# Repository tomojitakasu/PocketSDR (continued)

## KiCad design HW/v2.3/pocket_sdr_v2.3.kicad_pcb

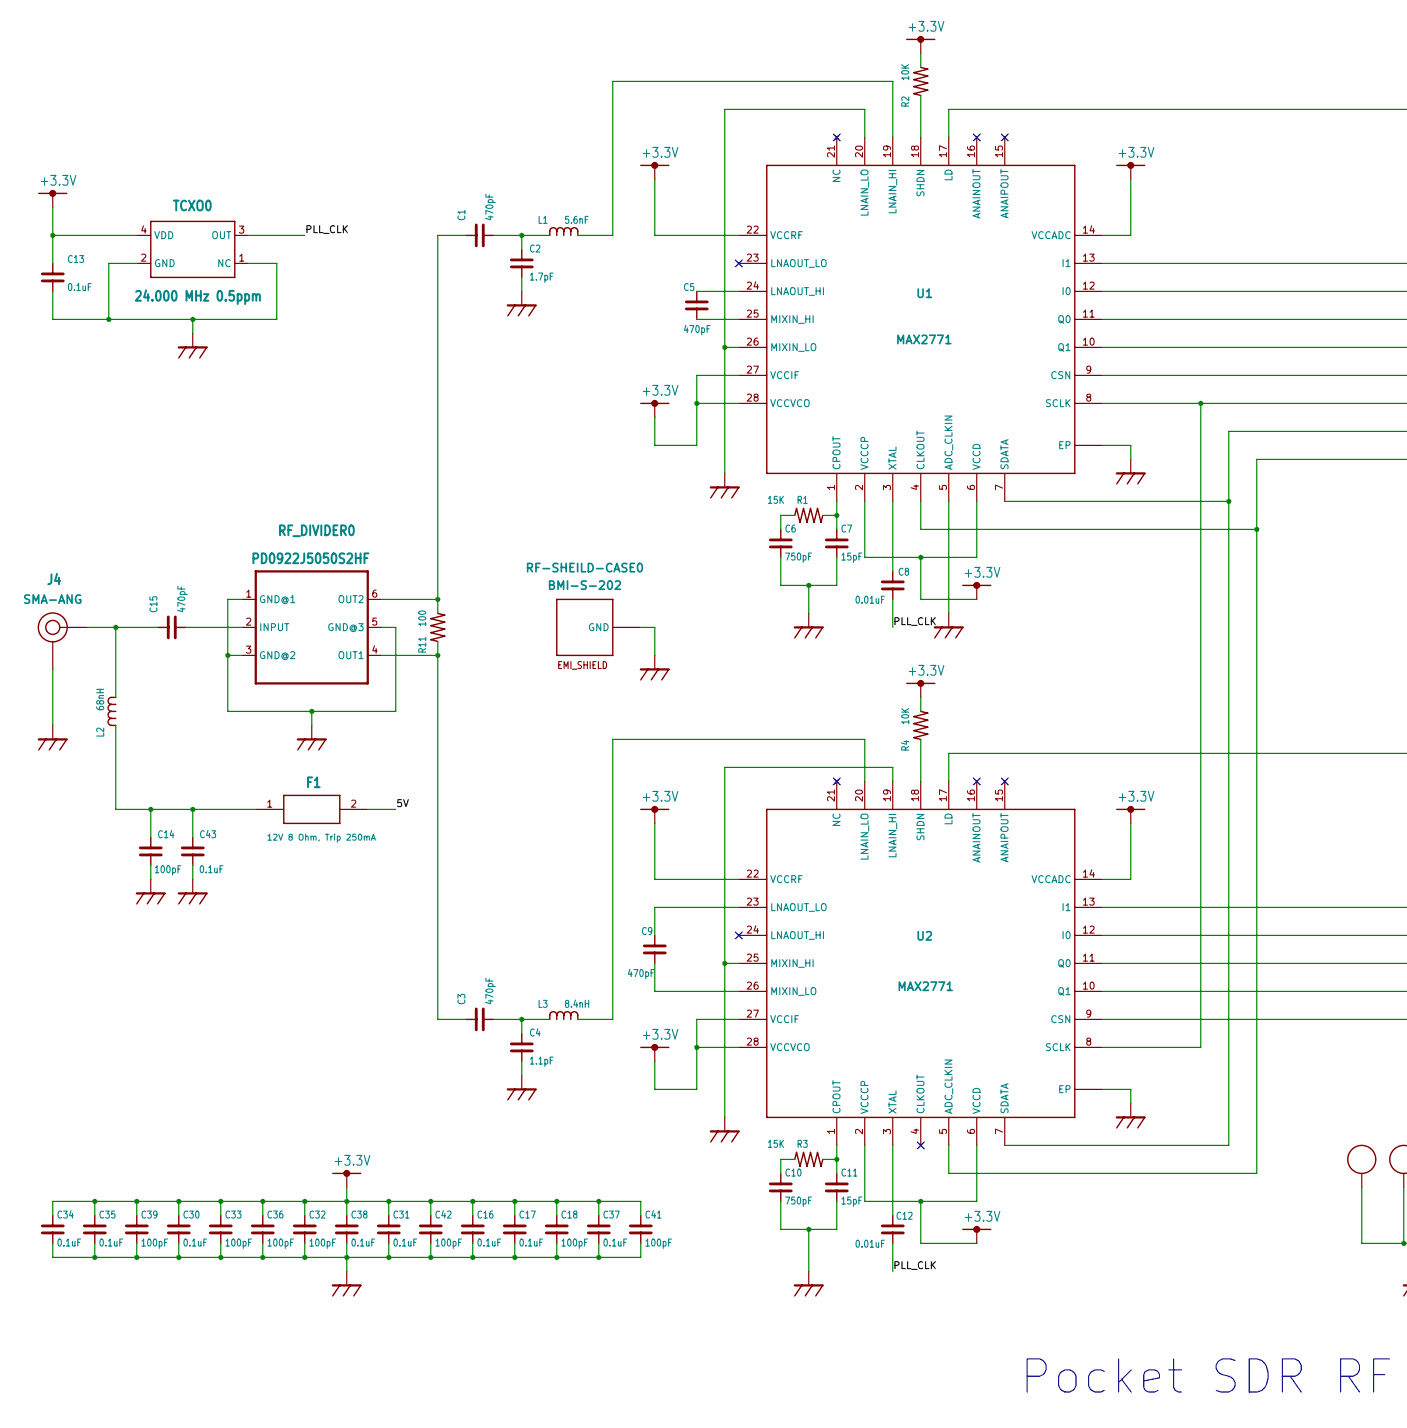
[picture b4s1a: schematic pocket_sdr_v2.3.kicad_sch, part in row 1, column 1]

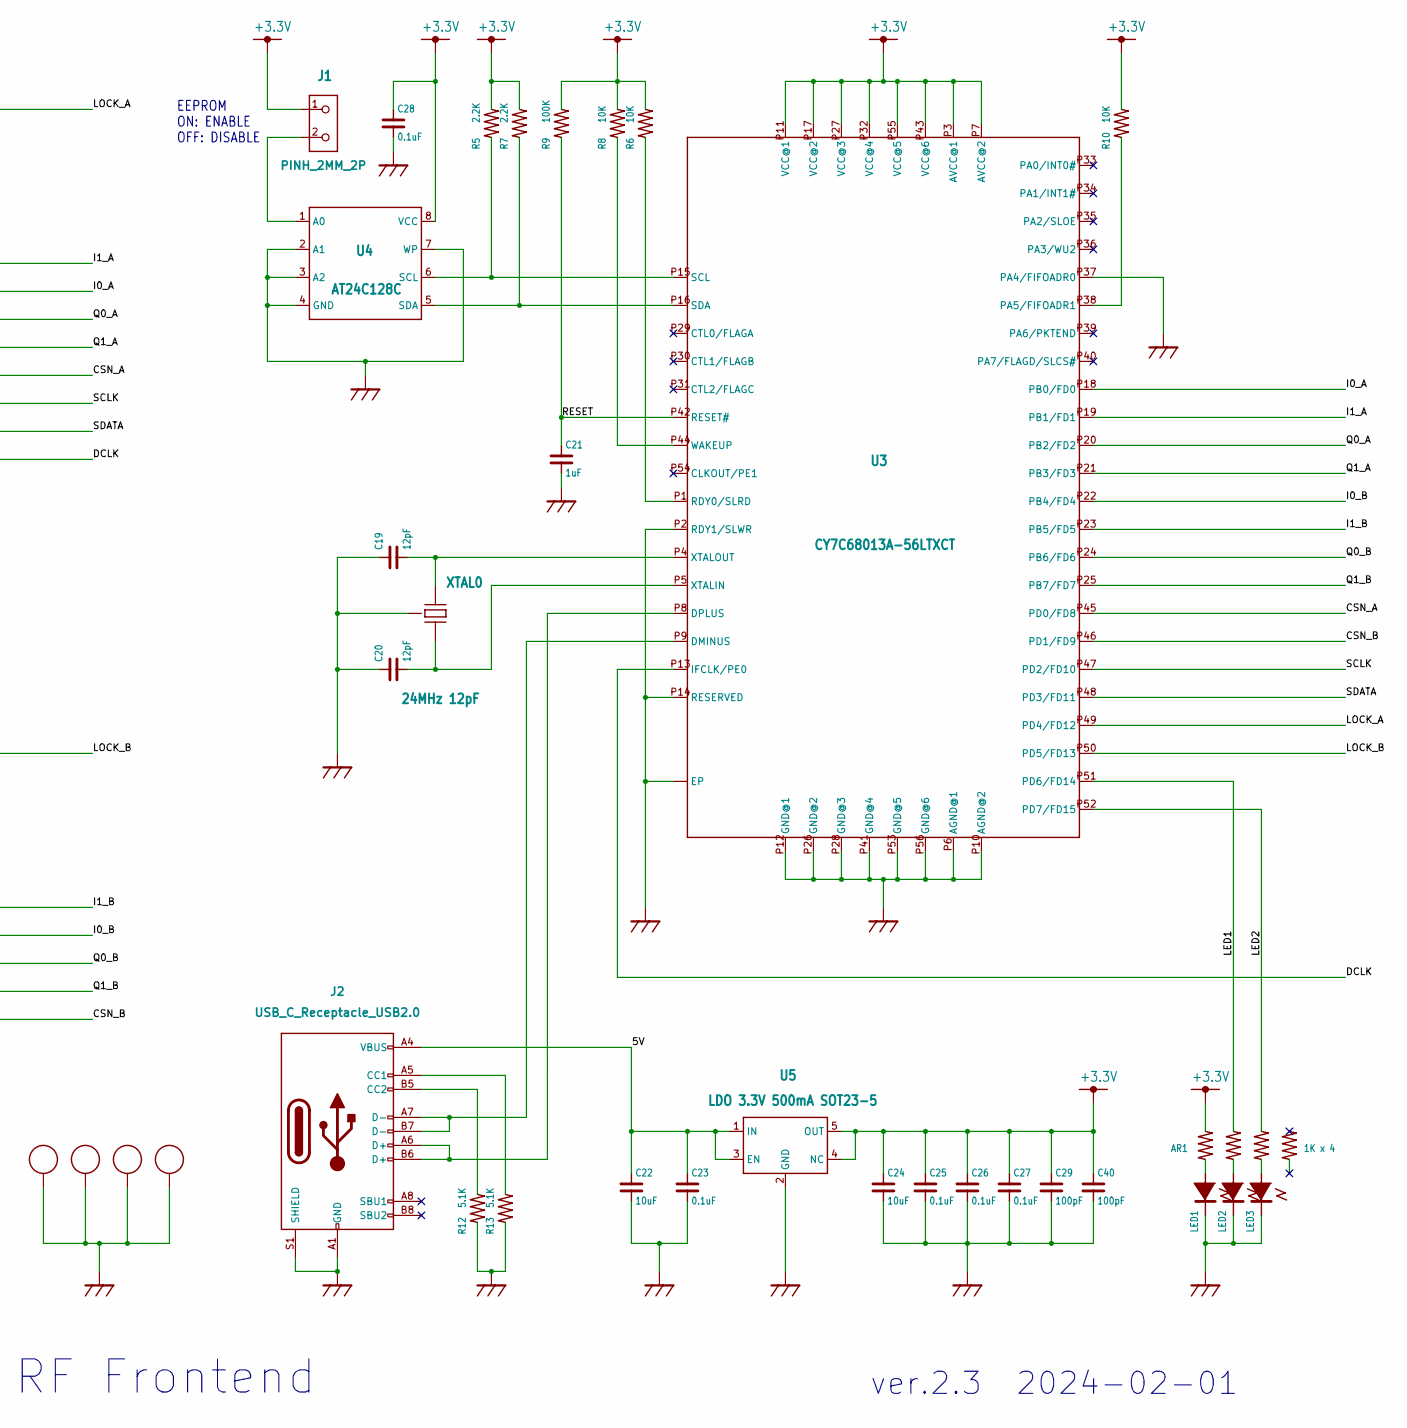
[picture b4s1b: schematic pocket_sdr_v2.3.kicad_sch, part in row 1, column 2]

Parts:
AR1: 1K x 4; EXB28V
C1, C3, C5, C9, C15: 470pF; C1005
C2: 1.7pF; C1005
C4: 1.1pF; C1005
C6, C10: 750pF; C1005
C7, C11: 15pF; C1005
C8, C12: 0.01uF; C1005
C13, C16, C17, C23, C25, C26, C27, C28, C30, C31, C34, C35, C37, C38, C43: 0.1uF; C1005
C14, C18, C29, C32, C33, C36, C39, C40, C41, C42: 100pF; C1005
C19, C20: 12pF; C1005
C21: 1uF; C1005
C22, C24: 10uF; C3225
F1: 12V 8 Ohm, Trip 250mA; C1608
J1: PINH_2MM_2P; PINH-2MM-2P
J2: USB_C_Receptacle_USB2.0
J4: SMA-ANG
L1: 5.6nF; C1608
L2: 68nH; C1608
L3: 8.4nH; C1608
LED1, LED2, LED3: LED1608; LED_1608
R1, R3: 15K; C1005
R2, R4, R6, R8, R10: 10K; C1005
R5, R7: 2.2K; C1005
R9: 100K; C1005
R11: 100; C1005
R12, R13: 5.1K; C1005
RF-SHEILD-CASE0: BMI-S-202
RF_DIVIDER0: PD0922J5050S2HF; RF_DIV
TCXO0: 24.000 MHz 0.5ppm; TCXO
U1, U2: MAX2771; TQFN28
U3: CY7C68013A-56LTXCT; QFN56
U4: AT24C128C; TSSOP_8P
U5: LDO 3.3V 500mA SOT23-5; SOT23
XTAL0: 24MHz 12pF; XTAL_SMD

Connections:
+3.3V: AR1.2, C13.1, C16.1, C17.1, C18.1, C24.P$1 (1), C25.1, C26.1, C27.1, C28.1, C29.1, C30.1, C31.1, C32.1, C33.1, C34.1, C35.1, C36.1, C37.1, C38.1, C39.1, C40.1, C41.1, C42.1, J1.1, R2.2, R4.2, R5.2, R6.2, R7.2, R8.2, R9.2, R10.2, TCXO0.4 (VDD), U1.2 (VCCCP), U1.6 (VCCD), U1.14 (VCCADC), U1.22 (VCCRF), U1.27 (VCCIF), U1.28 (VCCVCO), U2.2 (VCCCP), U2.6 (VCCD), U2.14 (VCCADC), U2.22 (VCCRF), U2.27 (VCCIF), U2.28 (VCCVCO), U3.P3 (AVCC@1), U3.P7 (AVCC@2), U3.P11 (VCC@1), U3.P17 (VCC@2), U3.P27 (VCC@3), U3.P32 (VCC@4), U3.P43 (VCC@6), U3.P55 (VCC@5), U4.8 (VCC), U5.4 (NC), U5.5 (OUT)
/5V: C22.P$1 (1), C23.1, F1.2, J2.A4 (VBUS), J2.A9 (VBUS), J2.B4 (VBUS), J2.B9 (VBUS), U5.1 (IN), U5.3 (EN)
/CSN_A: U1.9 (CSN), U3.P45 (PD0/FD8)
/CSN_B: U2.9 (CSN), U3.P46 (PD1/FD9)
/DCLK: U1.4 (CLKOUT), U2.5 (ADC_CLKIN), U3.P13 (IFCLK/PE0)
/I0_A: U1.12 (I0), U3.P18 (PB0/FD0)
/I0_B: U2.12 (I0), U3.P22 (PB4/FD4)
/I1_A: U1.13 (I1), U3.P19 (PB1/FD1)
/I1_B: U2.13 (I1), U3.P23 (PB5/FD5)
/LED1: AR1.4, U3.P51 (PD6/FD14)
/LED2: AR1.6, U3.P52 (PD7/FD15)
/LOCK_A: U1.17 (LD), U3.P49 (PD4/FD12)
/LOCK_B: U2.17 (LD), U3.P50 (PD5/FD13)
/PLL_CLK: C8.1, C12.1, TCXO0.3 (OUT)
/Q0_A: U1.11 (Q0), U3.P20 (PB2/FD2)
/Q0_B: U2.11 (Q0), U3.P24 (PB6/FD6)
/Q1_A: U1.10 (Q1), U3.P21 (PB3/FD3)
/Q1_B: U2.10 (Q1), U3.P25 (PB7/FD7)
/RESET: C21.1, R9.1, U3.P42 (RESET#)
/SCLK: U1.8 (SCLK), U2.8 (SCLK), U3.P47 (PD2/FD10)
/SDATA: U1.7 (SDATA), U2.7 (SDATA), U3.P48 (PD3/FD11)
GND: C2.1, C4.2, C6.2, C7.2, C10.2, C11.2, C13.2, C14.1, C16.2, C17.2, C18.2, C19.1, C20.1, C21.2, C22.P$2 (2), C23.2, C24.P$2 (2), C25.2, C26.2, C27.2, C28.2, C29.2, C30.2, C31.2, C32.2, C33.2, C34.2, C35.2, C36.2, C37.2, C38.2, C39.2, C40.2, C41.2, C42.2, C43.1, J2.A1 (GND), J2.A12 (GND), J2.B1 (GND), J2.B12 (GND), J2.S1 (SHIELD), J4.P2 (GND), J4.P3 (GND), J4.P4 (GND), J4.P5 (GND), LED1.2, LED2.2, LED3.2, R12.1, R13.1, RF-SHEILD-CASE0.P1 (GND), RF-SHEILD-CASE0.P2 (GND), RF-SHEILD-CASE0.P3 (GND), RF-SHEILD-CASE0.P4 (GND), RF-SHEILD-CASE0.P5 (GND), RF-SHEILD-CASE0.P6 (GND), RF-SHEILD-CASE0.P7 (GND), RF-SHEILD-CASE0.P8 (GND), RF-SHEILD-CASE0.P9 (GND), RF-SHEILD-CASE0.P10 (GND), RF-SHEILD-CASE0.P11 (GND), RF-SHEILD-CASE0.P12 (GND), RF_DIVIDER0.1 (GND@1), RF_DIVIDER0.3 (GND@2), RF_DIVIDER0.5 (GND@3), TCXO0.1 (NC), TCXO0.2 (GND), U1.5 (ADC_CLKIN), U1.20 (LNAIN_LO), U1.26 (MIXIN_LO), U1.C1 (EP), U1.C2 (EP), U1.C3 (EP), U1.C4 (EP), U1.EP, U1.V1 (EP), U1.V2 (EP), U1.V3 (EP), U1.V4 (EP), U1.V5 (EP), U1.V6 (EP), U1.V7 (EP), U1.V8 (EP), U1.V9 (EP), U2.19 (LNAIN_HI), U2.25 (MIXIN_HI), U2.C1 (EP), U2.C2 (EP), U2.C3 (EP), U2.C4 (EP), U2.EP, U2.V1 (EP), U2.V2 (EP), U2.V3 (EP), U2.V4 (EP), U2.V5 (EP), U2.V6 (EP), U2.V7 (EP), U2.V8 (EP), U2.V9 (EP), U3.EP1 (EP), U3.EP2 (EP), U3.EP3 (EP), U3.EP4 (EP), U3.EP5 (EP), U3.P2 (RDY1/SLWR), U3.P6 (AGND@1), U3.P10 (AGND@2), U3.P12 (GND@1), U3.P14 (RESERVED), U3.P26 (GND@2), U3.P28 (GND@3), U3.P37 (PA4/FIFOADR0), U3.P41 (GND@4), U3.P53 (GND@5), U3.P56 (GND@6), U3.P$1 (EP), U3.P$2 (EP), U3.P$3 (EP), U3.P$4 (EP), U3.P$5 (EP), U3.P$6 (EP), U3.P$7 (EP), U3.P$8 (EP), U3.P$9 (EP), U3.P$10 (EP), U3.P$11 (EP), U3.P$12 (EP), U3.P$13 (EP), U3.P$14 (EP), U3.P$15 (EP), U3.P$16 (EP), U3.P$17 (EP), U3.P$18 (EP), U3.P$19 (EP), U3.P$20 (EP), U4.2 (A1), U4.3 (A2), U4.4 (GND), U4.7 (WP), U5.2 (GND), XTAL0.P2 (GND), XTAL0.P4 (GND)
unnamed: AR1.1, LED1.1 (+)
unnamed: AR1.3, LED2.1 (+)
unnamed: AR1.5, LED3.1 (+)
unnamed: C14.2, C43.2, F1.1, L2.1
unnamed: J1.2, U4.1 (A0)
unnamed: J2.A5 (CC1), R13.2
unnamed: J2.B5 (CC2), R12.2
unnamed: C15.1, J4.P1 (RF), L2.2
unnamed: C1.2, C2.2, L1.1
unnamed: L1.2, U1.19 (LNAIN_HI)
unnamed: C3.2, C4.1, L3.1
unnamed: L3.2, U2.20 (LNAIN_LO)
unnamed: C6.1, R1.1
unnamed: C7.1, R1.2, U1.1 (CPOUT)
unnamed: R2.1, U1.18 (SHDN)
unnamed: C10.1, R3.1
unnamed: C11.1, R3.2, U2.1 (CPOUT)
unnamed: R4.1, U2.18 (SHDN)
unnamed: R5.1, U3.P15 (SCL), U4.6 (SCL)
unnamed: R6.1, U3.P1 (RDY0/SLRD)
unnamed: R7.1, U3.P16 (SDA), U4.5 (SDA)
unnamed: R8.1, U3.P44 (WAKEUP)
unnamed: R10.1, U3.P38 (PA5/FIFOADR1)
unnamed: C3.1, R11.1, RF_DIVIDER0.4 (OUT1)
unnamed: C1.1, R11.2, RF_DIVIDER0.6 (OUT2)
unnamed: C15.2, RF_DIVIDER0.2 (INPUT)
unnamed: C5.1, U1.24 (LNAOUT_HI)
unnamed: C5.2, U1.25 (MIXIN_HI)
unnamed: C8.2, U1.3 (XTAL)
unnamed: C9.1, U2.23 (LNAOUT_LO)
unnamed: C9.2, U2.26 (MIXIN_LO)
unnamed: C12.2, U2.3 (XTAL)
unnamed: J2.A7 (D-), J2.B7 (D-), U3.P9 (DMINUS)
unnamed: J2.A6 (D+), J2.B6 (D+), U3.P8 (DPLUS)
unnamed: C20.2, U3.P5 (XTALIN), XTAL0.P3 (XTAL2)
unnamed: C19.2, U3.P4 (XTALOUT), XTAL0.P1 (XTAL1)

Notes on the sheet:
Pocket SDR RF Frontend
EEPROM ON: ENABLE OFF: DISABLE
ver.2.3 2024-02-01

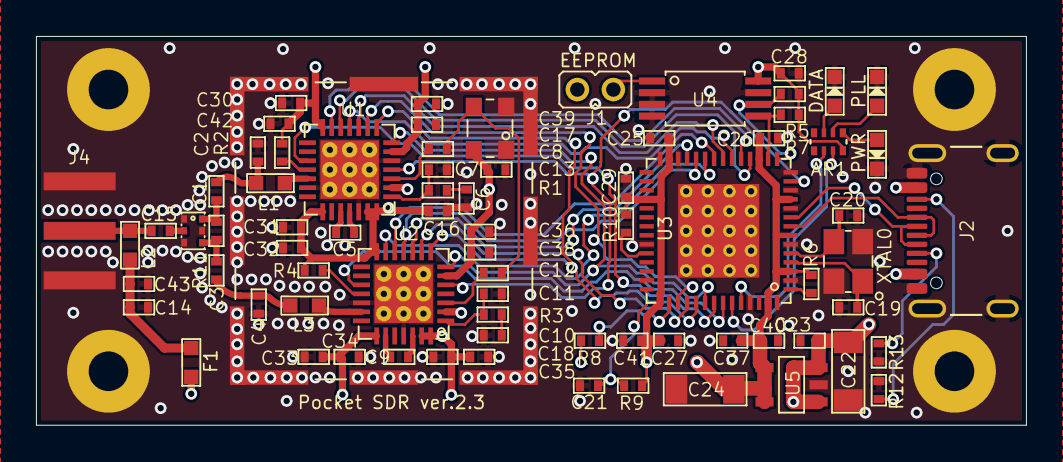
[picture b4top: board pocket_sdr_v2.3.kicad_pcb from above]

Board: 4 copper layers, 55.0 x 21.6 mm, 76 parts (0 on the bottom side), 58 nets.

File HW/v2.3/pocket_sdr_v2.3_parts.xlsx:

No | Part | Value | Package | Qty | Assembly | Supplier | Supplier Part # | Digi-Key Part # | Unit Price(Yen) | Price(Yen) | URL | NOTE
1 | U1, U2 | MAX2771 | TQFN28 | 2 | 2 | Maxim | MAX2771ETI+ | MAX2771ETI+-ND | 1631 | 3262 | https://www.digikey.jp/products/ja?keywords=MAX2771ETI%2B-ND
2 | U3 | EZ-USB FX2LP QFN56 | QFN56 | 1 | 1 | Cypress | CY7C68013A-56LTXCT | 428-4634-1-ND | 1857 | 1857 | https://www.digikey.jp/product-detail/ja/cypress-semiconduct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
3 | U4 | EEPROM 128Kbit I2C 8TSSOP | TSSOP_8P | 1 | 1 | Microchip | AT24C128C-XHM-T | AT24C128C-XHM-TCT-ND | 84 | 84 | https://www.digikey.jp/product-detail/ja/microchip-technolog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
4 | U5 | LDO 3.3V 500mA SOT23-5 | SOT23-5 | 1 | 1 | Nisshinbo | RP111N331D-TR-FE | 2129-RP111N331D-TR-FECT-ND | 171 | 171 | https://www.digikey.jp/products/ja?keywords=2129-RP111N331D-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
5 | RF_DIVIDER0 | 0805 Power Divider 50ohm 950 - 2150 MHz | 2.04 x 1.29 SMD | 1 | 1 | Anaren | PD0922J5050S2HF | 1173-1094-1-ND | 160 | 160 | https://www.digikey.jp/product-detail/ja/anaren/PD0922J5050S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
6 | TCXO0 | TCXO 24.000 MHz | 3.2 x 2.5 SMD | 1 | 1 | Epson | TG2520SMN 24.0000M-MCGNNM3 | - | 526.29999999999995 | 526.29999999999995 | https://www.mouser.jp/ProductDetail/Epson-Timing/TG2520SMN-2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
7 | XTAL0 | XTAL 24MHz SMD 12pF | 3.4 x 2.7 SMD | 1 | 1 | Wurth | 830108340709 | 1923-830108340709CT-ND | 126 | 126 | https://www.digikey.jp/products/ja?keywords=1923-830108340709CT-ND
8 | R1, R3 | 15K | R1005 | 2 | 2 | YAGEO | RC0402JR-0715KL | 311-15KJRCT-ND | 2.8 | 5.6 | https://www.digikey.jp/ja/products/detail/yageo/RC0402JR-071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
9 | R2, R4, R6, R8, R10 | 10K | R1005 | 5 | 5 | YAGEO | RC0402JR-0710KL | 311-10KJRCT-ND | 2.8 | 14 | https://www.digikey.jp/ja/products/detail/yageo/RC0402JR-071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
10 | R5, R7 | 2.2K | R1005 | 2 | 2 | YAGEO | RC0402JR-072K2L | 311-2.2KJRCT-ND | 2.8 | 5.6 | https://www.digikey.jp/ja/products/detail/yageo/RC0402JR-072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
11 | R9 | 100K | R1005 | 1 | 1 | YAGEO | RC0402JR-07100KL | 311-100KJRCT-ND | 2.8 | 2.8 | https://www.digikey.jp/ja/products/detail/yageo/RC0402JR-071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
12 | R11 | 100 | R1005 | 1 | 1 | YAGEO | RC0402JR-07100RL | 311-100JRCT-ND | 2.9 | 2.9 | https://www.digikey.jp/ja/products/detail/yageo/RC0402JR-071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
13 | R12, R13 | 5.1K | R1005 | 2 | 2 | YAGEO | RC0402FR-135K1L | 13-RC0402FR-135K1LCT-ND | 2.2999999999999998 | 4.5999999999999996 | https://www.digikey.jp/ja/products/detail/yageo/RC0402FR-135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
14 | AR1 | 1K x 4 RES ARRAY | EXB28V | 1 | 1 | Panasonic | EXB-28V102JX | Y7102CT-ND | 16 | 16 | https://www.digikey.jp/products/ja?keywords=Y7102CT-ND
15 | C1, C3, C5, C9, C15 | 470pF | C1005 | 5 | 5 | Kyocera | KGM05AR71H471KH | 478-KGM05AR71H471KHCT-ND | 4.5 | 22.5 | https://www.digikey.jp/ja/products/detail/kyocera-avx/KGM05A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
16 | C2 | 1.7pF | C1005 | 1 | 1 | Murata | GJM1555C1H1R7BB01D | 490-6074-1-ND | 10.6 | 10.6 | https://www.digikey.jp/ja/products/detail/murata-electronics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
17 | C4 | 1.1pF | C1005 | 1 | 1 | YAGEO | CC0402BRNPO9BN1R1 | 311-3321-1-ND | 6.2 | 6.2 | https://www.digikey.jp/ja/products/detail/yageo/CC0402BRNPO9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
18 | C6, C10 | 750pF | C1005 | 2 | 2 | Taiyo Yuden | UMK105CH751JVHF | 587-5098-1-ND | 11.1 | 22.2 | https://www.digikey.jp/ja/products/detail/taiyo-yuden/UMK105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
19 | C7, C11 | 15pF | C1005 | 2 | 2 | Kyocera | KGM05ACG1H150JH | 478-KGM05ACG1H150JHCT-ND | 5.0999999999999996 | 10.199999999999999 | https://www.digikey.jp/ja/products/detail/kyocera-avx/KGM05A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
20 | C8, C12 | 0.01uF | C1005 | 2 | 2 | Kyocera | KGM05AR71C103KH | 478-KGM05AR71C103KHCT-ND | 2 | 4 | https://www.digikey.jp/ja/products/detail/kyocera-avx/KGM05A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
21 | C13, C16, C17, C23, C25, C26, C27, C28, C30, C31, C34, C35, C37, C38, C43 | 0.1uF | C1005 | 15 | 15 | Kyocera | KGM05AR71C104KH | 478-KGM05AR71C104KHCT-ND | 2.2000000000000002 | 33 | https://www.digikey.jp/ja/products/detail/kyocera-avx/KGM05A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
22 | C14, C18, C29, C32, C33, C36, C39, C40, C41, C42 | 100pF | C1005 | 10 | 10 | Kyocera | KGM05ACG1H101JH | 478-KGM05ACG1H101JHCT-ND | 3.7 | 37 | https://www.digikey.jp/ja/products/detail/kyocera-avx/KGM05A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
23 | C19, C20 | 12pF | C1005 | 2 | 2 | Kyocera | KGM05ACG1H120JH | 478-KGM05ACG1H120JHCT-ND | 1.6 | 3.2 | https://www.digikey.jp/ja/products/detail/kyocera-avx/KGM05A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
24 | C21 | 1uF | C1005 | 1 | 1 | Kyocera | KGM05AR51A105KH | 478-KGM05AR51A105KHCT-ND | 11 | 11 | https://www.digikey.jp/ja/products/detail/kyocera-avx/KGM05A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
25 | C22, C24 | 10uF | C3216 | 2 | 2 | Samsung | CL31B106MOHNNNE | 1276-6641-1-ND | 20.399999999999999 | 40.799999999999997 | https://www.digikey.jp/ja/products/detail/samsung-electro-me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
26 | L1 | 5.6nH | L1608 | 1 | 1 | Murata | LQW18AN5N6D00D | 490-1164-1-ND | 23 | 23 | https://www.digikey.jp/ja/products/detail/murata-electronics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
27 | L2 | 68nH | L1608 | 1 | 1 | Murata | LQW18AN68NJ00D | 490-1178-1-ND | 23 | 23 | https://www.digikey.jp/ja/products/detail/murata-electronics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
28 | L3 | 8.4nH | L1608 | 1 | 1 | Murata | LQW18AN8N4C8ZD | 490-15752-1-ND | 39 | 39 | https://www.digikey.jp/ja/products/detail/murata-electronics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
29 | LED1, LED2, LED3 | LED1608 White | LED1608 | 3 | 3 | QT Brightek | QBLP601-IW | 1516-1057-1-ND | 59 | 177 | https://www.digikey.jp/ja/products/detail/qt-brightek-qtb/QB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
30 | J1 | PIN HEADER 2MM 2P | PINH-2MM-2P | 1 | 0 | Harwin | M22-2510205 | 952-1311-ND | 31 | 31 | https://www.digikey.jp/ja/products/detail/harwin-inc/M22-251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
31 | J2 | USB-C RECEPTACLE SMT USB2.0 | USB-C SMT | 1 | 1 | GCT | USB4105-GF-A | 2073-USB4105-GF-ACT-ND | 126 | 126 | https://www.digikey.jp/ja/products/detail/gct/USB4105-GF-A/11198441
32 | J4 | SMA JACK EDGE MNT | SMA JACK EDGE MNT | 1 | 0 | uxcell | - | - | 157.6 | 157.6 | https://www.amazon.co.jp/uxcell-a11053100ux0317-RF%E3%82%B3%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
33 | J1-S | CONN SHUNT 2MM | CONN SHUNT 2MM | 1 | 0 | Sullins Connector | SPN02SYBN-RC | S3404-ND | 20 | 20 | https://www.digikey.jp/ja/products/detail/sullins-connector-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
34 | RF-SHEILD-CASE | RF SHIELD 0.65" x 0.65" SOLDER | 0.65" x 0.65" | 1 | 0 | Laird | BMI-S-202-F | 903-1051-1-ND | 312 | 312 | https://www.digikey.jp/products/ja?keywords=903-1051-1-ND
35 | RF-SHEILD-CASE-C | RF SHIELD 0.668"x0.668" SNAP FIT | 0.668" x 0.668" | 1 | 0 | Laird | BMI-S-202-C | 903-1014-ND | 279 | 279 | https://www.digikey.jp/products/ja?keywords=903-1014-ND279
36 | F1 | PolySwitch 12V, 8 Ohm, Trip 250 mA | R1608 | 1 | 1 | Littelfuse Inc | FEMTOSMDC010F-2 | FEMTOSMDC010F-2 | 123 | 123 | https://www.digikey.jp/ja/products/detail/littelfuse-inc/FEM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
 | Subtotal |  |  | 78 | 73 |  |  |  |  | 7749.1000000000013
37 | PCB | FR4 1.6mm 4 layer | 21.6 x 55.0 mm | 1 | 0 | JLCPCB |  |  | 207.11056000000005 | 207.11056000000005 | https://jlcpcb.com/ | 10 pcs
38 | PCB Assembly |  |  | 1 | 0 |  |  |  |  |  | https://jlcpcb.com/ | 10 pcs
 | Case
39 | Aluminum Pipe | 25 x 15 x 1.5 x 55 mm |  | 1 | 0 | Yokoyama Techno |  |  | 233.99397590361446 | 233.99397590361446 | https://www.yokoyama-techno.net/detail/50.html | 10 pcs
40 | Panel | 25 x 15 mm Nylon white, Front and Back |  | 1 | 0 | DMM.make 3D print |  |  | 338.83333333333331 | 338.83333333333331 | https://make.dmm.com/print/ | 6 pcs
41 | Screw | M2 x 10 Sara |  | 4 | 0 | Monotaro |  |  | 9.1538461538461533 | 36.615384615384613 | https://www.monotaro.com/p/0832/7435
42 | Nut | M2 |  | 4 | 0 | Monotaro |  |  | 3.2666666666666666 | 13.066666666666666 | https://www.monotaro.com/p/5068/7148/
43 | USB Cable | USB 2.0 A Male - USB-C Male 0.5 m |  | 1 | 0 | Akizuki |  |  | 100 | 100 | https://akizukidenshi.com/catalog/g/g117017/
 | Total |  |  |  |  |  |  |  |  | 8678.7199205190009

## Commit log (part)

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2025-03-19 Add Help link in Help dialog.
2025-03-19 Added.
2025-03-19 Deleted.
2025-03-19 Add excluded.
2025-03-19 Updated.
2025-03-19 Fix HELP_LINK.
2025-03-20 Fixed.
2025-03-20 ver.0.14.
2025-03-21 Fix segfault.
2025-03-21 Fix bulk transfer error for FE 2CH.
2025-03-26 Fixed #45.
2025-03-27 Add default values of log_mask.
2025-03-27 http -> https.
2025-03-30 Fixed #40.
2025-03-30 Fixed sampling rate option disabled.
2025-04-08 Fixed segfault for INT8X2 format input.
2025-04-13 Fixed #39.
2025-09-26 sdr_corr_max: match header arg order to impl
2025-11-11 Updated types.
2025-11-11 Support IBYTE, ISHORT as input formats.
2025-11-11 fix symbol table access violation problem
2025-11-19 Update constants, types, APIs.
2025-11-19 Improved carrier-phase coherency.
2025-11-19 Minor fix.
2025-11-19 Fixed comment.
2025-11-19 add API sdr_cpx_fft(), modify API sdr_tag_read(), sdr_tag_write()
2025-11-19 Update time offsets.
2025-11-19 Enabled L1C/B for PVT.
2025-11-19 support alternative RF frontends.
2025-11-19 support alternative RF frontends
2026-04-18 Refactored.
2026-04-18 Change API name.
2026-04-19 Added jammers.
2026-04-22 Added API sdr_lpf_new(), sdr_lpf_free(), sdr_lpf_apply().
2026-04-22 Followed thread API changes.
2026-04-22 Add Galileo E5a-QP.
2026-04-22 Followed thread API change.
2026-04-22 Added API sdr_thread_create(), sdr_thread_join(), sdr_mutex_init(), sdr_mutex_lock(), sdr_mutex_unlock().
2026-04-22 Localized CyAPI.
2026-04-22 Added [CHALL] section.
2026-04-22 Updated types, APIs.
2026-04-22 Updated ant body-fixed frame.
2026-04-22 Added LPF for RF CHs.
2026-04-25 Improve codes.
2026-04-25 Update comments.
2026-04-25 Added RTCM3 RF CH separation.
2026-04-25 Fix TCP client stream bug.
2026-04-26 ver.0.15b.
2026-04-26 Added constant FILT_CN0.
2026-04-26 LS -> KF.
2026-04-26 Added composite array CH.
2026-04-26 Added array options.
2026-04-26 improve performance.
2026-04-26 Updated error massages.
2026-04-28 Moved from build.
2026-04-28 Added libpocketfft.mk
2026-04-28 Use $<.
2026-04-29 Zero fill for dropped samples.
2026-04-30 Move libusb_transfer to sdr_usb.c.
2026-04-30 SDR_MAX_BUFF -> SDR_MAX_UBUFF.
2026-04-30 Follows API changes.
2026-04-30 Added ELE GAIN.
2026-04-30 Fixed typo.
2026-04-30 Added option -b.
2026-04-30 Added API sdr_corr_std_cpx_code().
2026-04-30 Supported E5ABQ.
2026-04-30 Added E5ABQ.
2026-04-30 Update types.
2026-05-01 Fix bugs.
2026-05-01 Fix bug.
2026-05-01 Suppress warning.
2026-05-01 Change array scale.
2026-05-02 Refactored array calibration and beam-forming.
2026-05-02 Add E5ABQ.
2026-05-02 Add plot_image(), plot_sky_mask().
2026-05-02 Refactored array calibration / beam-forming API.
    Move calib save/load into libsdr (sdr_array_{save,load}_calib +
    sdr_rcv wrappers), split sdr_array_config into sdr_array_run /
    sdr_array_inject, drop redundant nrfch parameter (snapshot in
    sdr_array_t), strip obs screening already covered by build_meas,
    and prune internal NULL guards now that callers are validated.
2026-05-02 Updated API reference for array calibration / beam-forming refactor.
2026-05-02 Update comment.
2026-05-02 Refactored array calibration / beam-forming API.
    Renamed: sdr_array_step -> sdr_array_calib (merged with the now-static
    old sdr_array_calib body), sdr_array_inject -> sdr_array_set,
    sdr_array_{save,load}_calib -> sdr_array_{save,load}, and the matching
    sdr_rcv_array_calib -> sdr_rcv_array_run / sdr_rcv_array_step ->
    sdr_rcv_array_calib / sdr_rcv_array_{save,load}_calib ->
    sdr_rcv_array_{save,load}. Per-arch beam initialization moved out of
2026-05-02 Speed up array beam combining and clean up array API.
    Beam combining: precompute per-CH 256-entry LUT (cpx8 byte ->
    weighted (re, im) contribution) in sdr_arch_set_beam() and reduce
    sdr_arch_combine() to load + add. Measured ~2x throughput improvement
    at narch=8 (52.7 -> 104 MB/s in 10x file playback), giving ~1.6x
    real-time margin at fs=16 MHz x 8 array CHs. Re/im pair stored
    interleaved as sdr_lut_t for locality.
2026-05-02 Update trace level.
2026-05-02 ver.0.15.
2026-05-02 Moved to ../build_msvc.
2026-05-03 Fix bug on generating sec-code index.
2026-05-03 Fix problem to overflow obs data buffer in array.
2026-05-03 Add rise of timer resolution for Windows.
2026-05-04 switch includes for FFT.
2026-05-04 Move AltBOC related codes to sdr_ch.c.
2026-05-04 Fallback KF to LS if residual RMS exceeds limit.
2026-05-04 Output $CH log without PVT fix.
2026-05-04 Support E5 AltBOC, DLL, PLL filter -> 2nd, 3rd order.
2026-05-04 Update constants and types.
2026-05-04 Change API sdr_rcv_sel_ch().
2026-05-04 Upgrade correlator plot.
2026-05-04 ver.0.15b2
2026-05-04 Follow API change.
2026-05-04 ver.0.15b2.
2026-05-05 Add scale in correlation plot.
2026-05-05 Add receiver option -BUMP_K=.
2026-05-05 Add E5a-E5b offset correction for AltBOC.
2026-05-05 Update blank line.
2026-05-06 Update global options.
2026-05-06 Adjust layout.
2026-05-06 Array Calibration enable if narch <= 0.
2026-05-06 Fix label.
2026-05-07 Add array calibration modes.
2026-05-07 Add Clear button in Array Option dialog.
2026-05-07 matplotlib -> sdr_plot.py.
2026-05-07 Add I * sign(IP) average for correlator statistics.
2026-05-07 Add AveI for correlator plot.
2026-05-08 Fix style.
2026-05-08 Fix bump-jump for G1OCP, G2OCP.
2026-05-09 Fix unrecognized PlutoSDR in RaspiOS.
2026-05-09 Adjust button size.
2026-05-09 Change widget style for macOS and Linux.
2026-05-09 -Ofast -> -O3.
2026-05-09 sprintf() -> snprintf().
2026-05-09 Refer command_ref.md.
2026-05-09 Fix macOS problem.
2026-05-09 Moved to pocket_trk.sh.
2026-05-09 Fix maxOS problem.
2026-05-09 Supress warnings.
2026-05-09 Supress warning.
2026-05-09 fftw3 -> pocketfft.
2026-05-09 fftw -> pocketfft.
2026-05-11 Add soapy log.
2026-05-11 IQ independent AGC.
2026-05-11 v.0.15.
2026-05-11 Update layout.
2026-05-11 Add airspy as device.
2026-05-11 Add -fd option.
2026-05-11 Follow -fd option.
2026-05-11 Moved to lib/SoapySDR.
2026-05-11 Deleted or moved.
2026-05-11 Update sytle. document link: internal -> github.
2026-05-30 Add Airspy Mini.
2026-05-30 Add page break.
2026-05-30 Add support CS16 in read_data.
2026-05-30 Support E5AQP code.
2026-05-30 Add option -fmt.
2026-05-30 Write tag file before capture.
2026-05-30 Fix RF CH assignment bug for FE 4CH (SDR_FMT_RAW16).
2026-06-01 Add almanac decoder functions for GLO,GAL,BDS.
2026-06-01 Add almanac decoder functions.
2026-06-01 Add receiver clock rate in solution.
2026-06-01 Reflect API changes.
2026-06-01 Support SoapySDR devices.
2026-06-01 Add make option USE_SOAPY, USE_FFTW.
2026-06-01 Add make option USE_FFTW.
2026-06-01 Add $ALM log, Fast-Search acquisition mode.
2026-06-01 Add Signal Acquisition Mode in System Options.
2026-06-01 ver.0.16.
2026-06-01 Add #ifdef SOAPYSDR.
2026-06-01 Add almanac decoder for GLO,GAL,BDS.
2026-06-01 Add almanac decoding, save and load.
2026-06-01 Add fast acquisition mode.
2026-06-01 Add $ALM in log_types[].
2026-06-01 Support format CS8 and CS16.
2026-06-01 Add make option USE_FFTW, USE_SOAPY.
2026-06-01 Add option max-acq.
2026-06-01 Change default output logs.
2026-06-01 fix: V-003 security vulnerability
    Automated security fix generated by OrbisAI Security
2026-06-01 fix: add bounds check before memcpy in sdr_nav.c
    The code uses a 'type' variable derived from navigation message content to compute a destination offset for memcpy
2026-06-01 Update Input Options Dialog.
2026-06-01 Fix github latex problem.
2026-06-01 Fix github md viewer latex problem.
2026-06-01 Fix github md parser problems.
2026-06-03 Fix pseudorange offset problem.
2026-06-04 Moved from .. .
2026-06-04 Added for unit tests.
2026-06-04 Moved to ./script or ./python.
2026-06-04 Updates for unit tests.
2026-06-04 Update directory structure.
2026-06-05 Fix CS16 (little-endian) in IF Data File Formats.
2026-06-06 LDPC-codes -> internal implementation.
2026-06-06 LIBFEC -> internal implementation.
2026-06-06 sdr_corr_std performance as np=4.
2026-06-06 Update tests of sdr_decode_conv() and sdr_decode_rs().
2026-06-13 Rise timer resolution for Windows.
2026-06-13 Hard-decision -> soft-decision.
2026-06-13 Update symbol-sync algorithm in symb_sync().
2026-06-14 MAX_RMS: 0.015 -> 0.020.
2026-06-14 Add THRES_SEC_RATIO for sec-code-sync.
2026-06-14 Add receiver option -LOG_LEVEL=n.
2026-06-14 ver.0.17.
2026-06-14 Improved symbol-sync.
2026-06-14 Updated for Linux, macOS.
2026-06-14 Add Options [Load], [Save] buttons.
2026-06-14 Add [Set Default] in System Options, [Set All], [Unset All] in Signal Options.
2026-06-14 Added for Codex and Claude Code.
2026-06-15 Update START, STOP log.
2026-06-15 Update symbol sync logic.
2026-06-15 Update loss-of-lock detection logic.
2026-06-15 Add system option Carrier Lock Threshold (PLI) and Lost Decision Count (windows).
2026-06-15 Add system options.
2026-06-17 Remove link of libfec.a and libldpc.a.
2026-06-17 Add options thres_pli and lost_th.
2026-06-17 Add phi to sdr_ch_t.
2026-06-17 Update style.
2026-06-17 Add PLI in print_ch_stat().
2026-06-17 Fix carrier phase update logic. Fix bug to switch WB_FLL and NB_FLL.
2026-06-17 Add [To RINEX] button in Output Options dialog.
2026-06-17 Fix carrier phase logic in tracking loop.
2026-06-17 Default lag_epoch option: 0.5 -> 0.8 s.
2026-06-17 Suppress warnings.
2026-06-17 Add make option USE_AVX2=x.
2026-06-17 Update UI layout.
2026-06-17 Fix invalid pseudorange.
2026-06-18 No output $OBS if pseudorange missing.
2026-06-18 Update time offset table.
2026-06-19 Update Documents.
2026-06-19 Fix document URL.
2026-06-19 Fix URL path.
2026-06-21 LO Freq input: Entry -> Combobox in Input Options Dialog.
